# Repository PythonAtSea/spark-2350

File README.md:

# spark!2350

## What is this?

The spark!2350 is a RP2350 based microcontroller that has a RM2 chip for BLE and WiFi. It also has a LiPo battery charger, as it is designed for use in mireless keyboards. It also has a user accesable NeoPixel, and a variable charge rate. 

## Why?

I saw the release of the RM2 and I immediatly knew I wanted to make something with it. I've always thought the nice!nano was cool, so I kinda made that, although this is designed for maximum GPIO availibility, not small size. 

made with <3 and insanity.

## BOM

| Name | Link | Price |
|---|---|---|
| RPI RM2 | https://shop.pimoroni.com/products/raspberry-pi-radio-module | $4 |
| Pimoroni shpping | n/a | $14 |
| JLC PCBA | N/A | $78.28 |
| JLC shipping | N/A | $38.52 |
| Total | N/A | $134.80 |

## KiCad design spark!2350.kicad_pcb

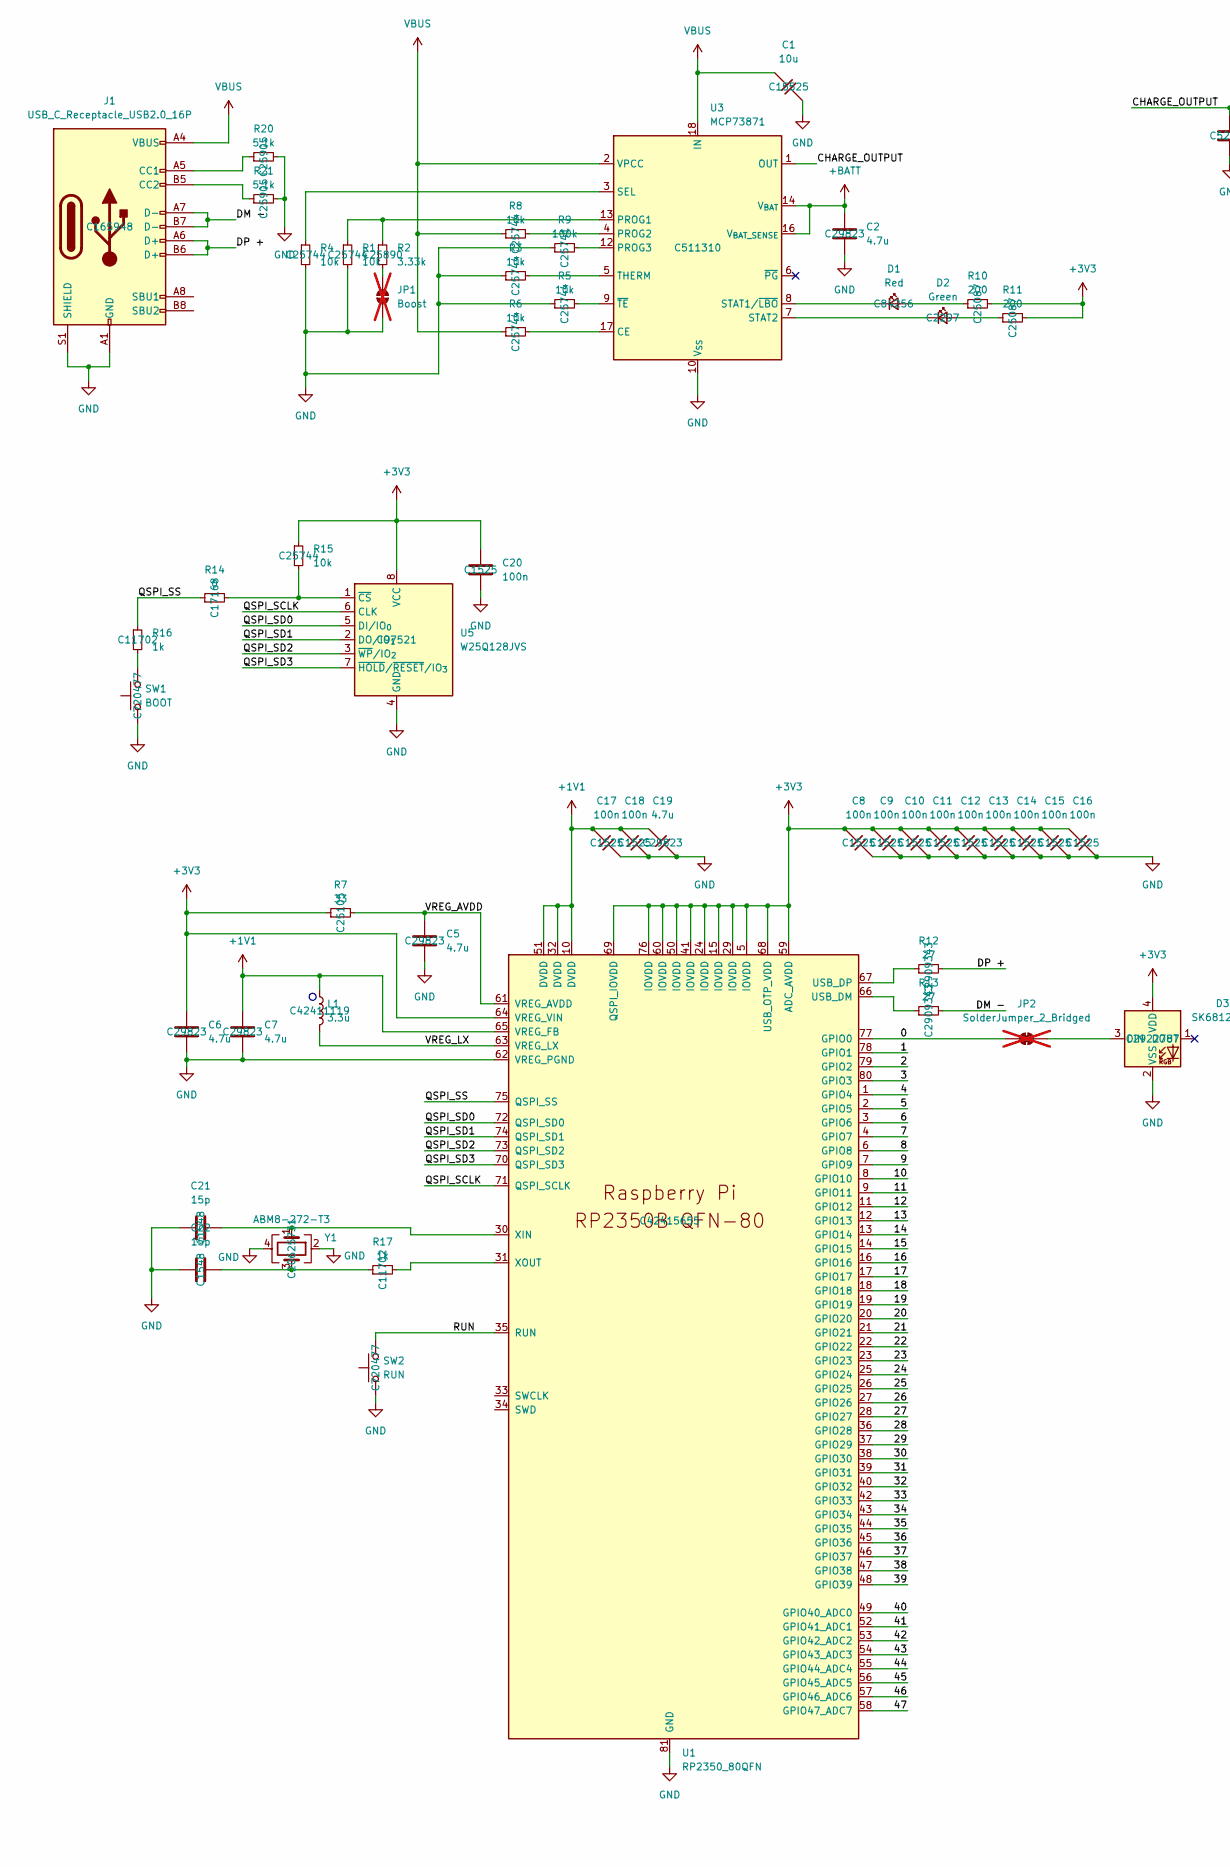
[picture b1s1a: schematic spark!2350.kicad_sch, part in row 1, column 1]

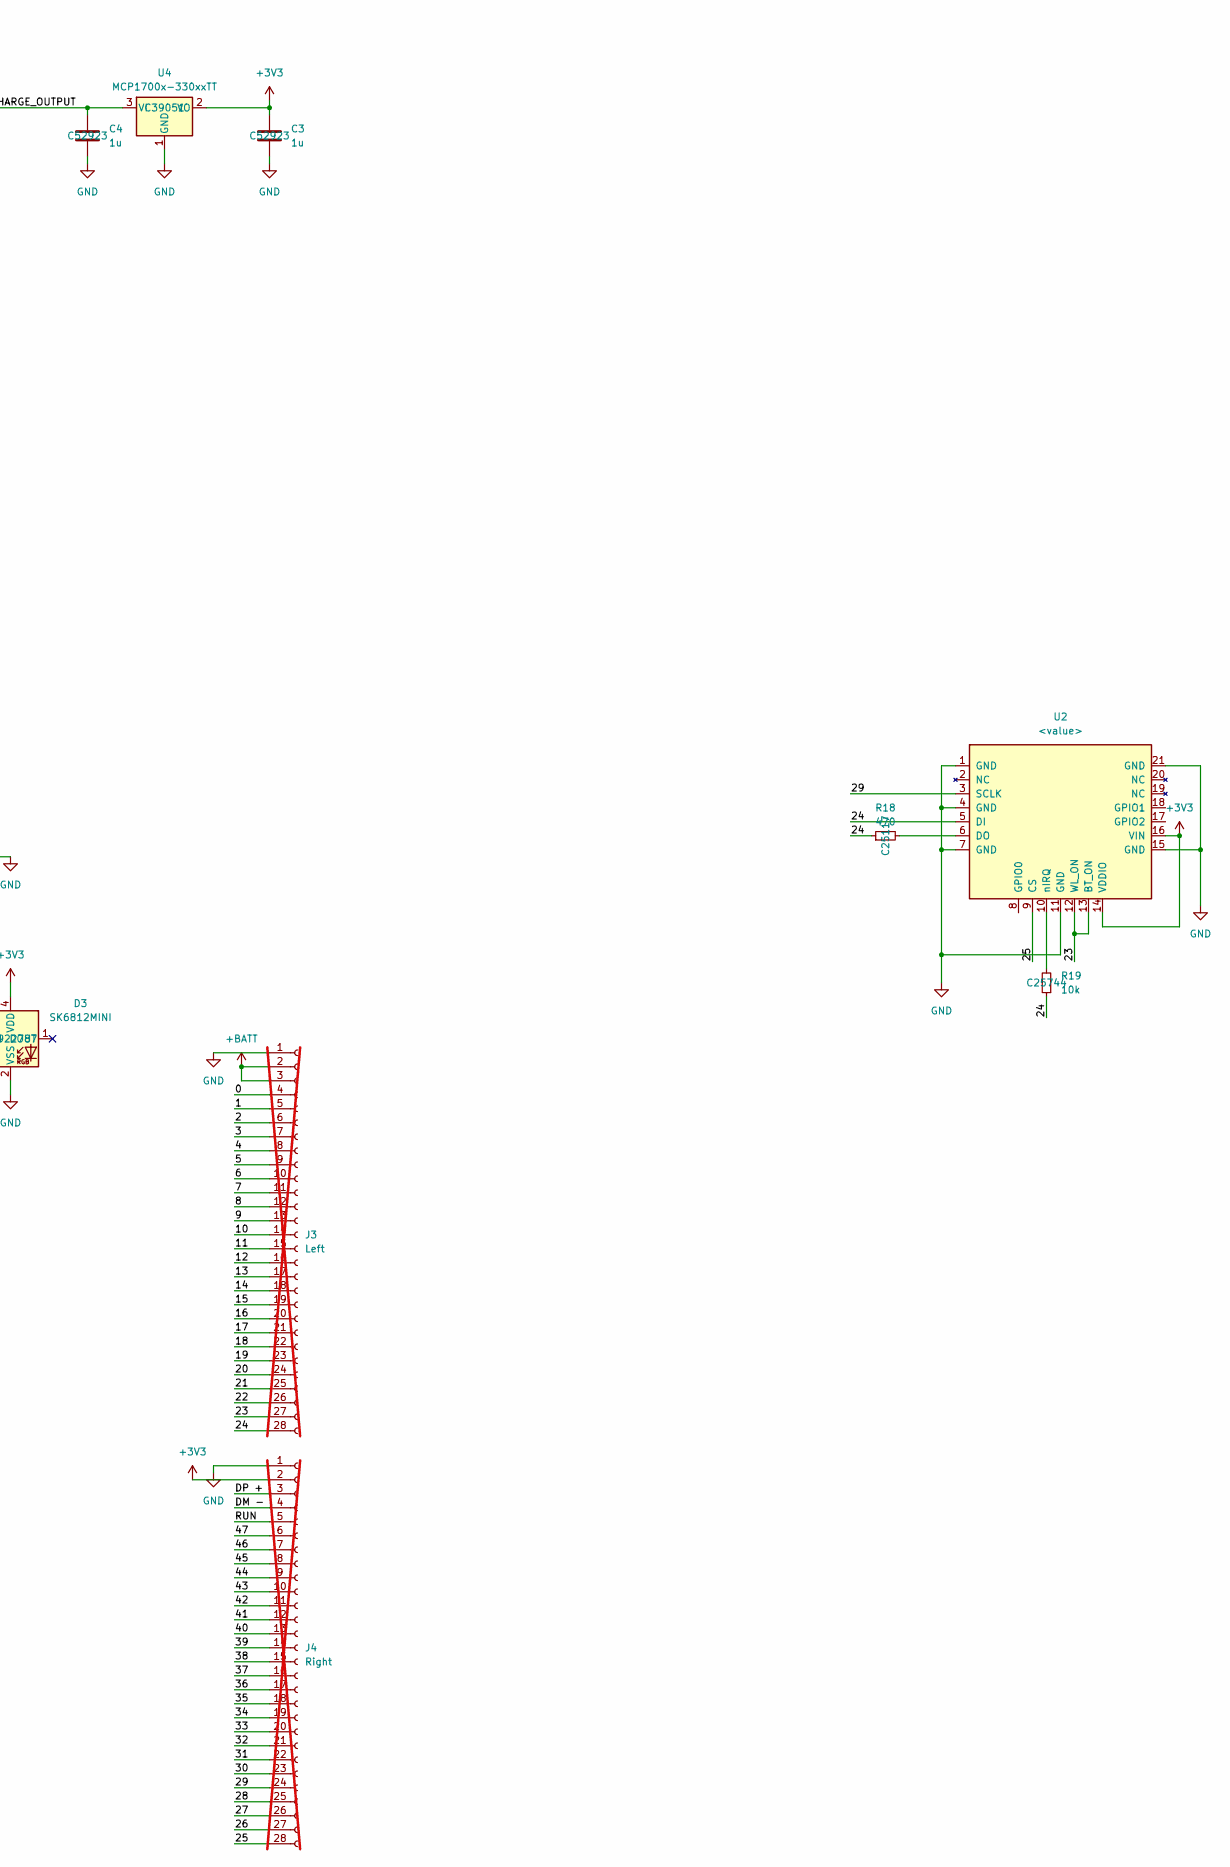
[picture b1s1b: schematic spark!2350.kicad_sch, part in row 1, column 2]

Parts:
C1: 10u; C_0402_1005Metric_small_pads; LCSC C15525
C2, C5, C6, C7, C19: 4.7u; C_0402_1005Metric_small_pads; LCSC C29823
C3, C4: 1u; C_0402_1005Metric_small_pads; LCSC C52923
C8, C9, C10, C11, C12, C13, C14, C15, C16, C17, C18, C20: 100n; C_0402_1005Metric_small_pads; LCSC C1525
C21, C22: 15p; C_0402_1005Metric_small_pads; LCSC C1548
D1: Red; LED_0805_2012Metric; LCSC C84256
D2: Green; LED_0805_2012Metric; LCSC C2297
D3: SK6812MINI; LED_SK6812MINI_PLCC4_3.5x3.5mm_P1.75mm; LCSC C2922787
J1: USB_C_Receptacle_USB2.0_16P; USB_C_Receptacle_HRO_TYPE-C-31-M-12; LCSC C165948
J3: Left; 27right; not fitted
J4: Right; 27left; not fitted
JP1: Boost; SolderJumper-2_P1.3mm_Open_RoundedPad1.0x1.5mm; not fitted
JP2: SolderJumper_2_Bridged; SolderJumper-2_P1.3mm_Bridged_RoundedPad1.0x1.5mm; not fitted
L1: 3.3u; L_pol_2016; LCSC C42411119
R1, R3, R4, R5, R6, R8, R15, R19: 10k; R_0402_1005Metric; LCSC C25744
R2: 3.33k; R_0402_1005Metric; LCSC C25890
R7: 33; R_0402_1005Metric; LCSC C25105
R9: 100k; R_0402_1005Metric; LCSC C25741
R10, R11: 200; R_0402_1005Metric; LCSC C25087
R12, R13: 27; R_0402_1005Metric; LCSC C2909343
R14: 0; R_0402_1005Metric; LCSC C17168
R16, R17: 1k; R_0402_1005Metric; LCSC C11702
R18: 470; R_0402_1005Metric; LCSC C25117
R20, R21: 5.1k; R_0402_1005Metric; LCSC C25905
SW1: BOOT; SW_TS-1088-AR02016; LCSC C720477
SW2: RUN; SW_TS-1088-AR02016; LCSC C720477
U1: RP2350_80QFN; RP2350-QFN-80-1EP_10x10_P0.4mm_EP3.4x3.4mm_ThermalVias; LCSC C42415655
U2: <value>; rpi_rmc20452t
U3: MCP73871; QFN-20-1EP_4x4mm_P0.5mm_EP2.5x2.5mm; LCSC C511310
U4: MCP1700x-330xxTT; SOT-23; LCSC C39051
U5: W25Q128JVS; SOIC-8_5.3x5.3mm_P1.27mm; LCSC C97521
Y1: ABM8-272-T3; ABM8-272-T3_ABR; LCSC C20625731

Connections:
+1V1: C7.1, C17.2, C18.2, C19.2, L1.1, U1.10 (DVDD), U1.32 (DVDD), U1.51 (DVDD), U1.65 (VREG_FB)
+3V3: C3.1, C6.1, C8.2, C9.2, C10.2, C11.2, C12.2, C13.2, C14.2, C15.2, C16.2, C20.1, D3.4 (VDD), J4.2, R7.1, R10.2, R11.2, R15.1, U1.5 (IOVDD), U1.15 (IOVDD), U1.24 (IOVDD), U1.29 (IOVDD), U1.41 (IOVDD), U1.50 (IOVDD), U1.59 (ADC_AVDD), U1.60 (IOVDD), U1.64 (VREG_VIN), U1.68 (USB_OTP_VDD), U1.69 (QSPI_IOVDD), U1.76 (IOVDD), U2.14 (VDDIO), U2.16 (VIN), U4.2 (VO), U5.8 (VCC)
+BATT: C2.1, J3.2, J3.3, U3.14 (V_{BAT}), U3.15 (V_{BAT}), U3.16 (V_{BAT_SENSE})
/0: J3.4, JP2.1 (A), U1.77 (GPIO0)
/1: J3.5, U1.78 (GPIO1)
/2: J3.6, U1.79 (GPIO2)
/3: J3.7, U1.80 (GPIO3)
/4: J3.8, U1.1 (GPIO4)
/5: J3.9, U1.2 (GPIO5)
/6: J3.10, U1.3 (GPIO6)
/7: J3.11, U1.4 (GPIO7)
/8: J3.12, U1.6 (GPIO8)
/9: J3.13, U1.7 (GPIO9)
/10: J3.14, U1.8 (GPIO10)
/11: J3.15, U1.9 (GPIO11)
/12: J3.16, U1.11 (GPIO12)
/13: J3.17, U1.12 (GPIO13)
/14: J3.18, U1.13 (GPIO14)
/15: J3.19, U1.14 (GPIO15)
/16: J3.20, U1.16 (GPIO16)
/17: J3.21, U1.17 (GPIO17)
/18: J3.22, U1.18 (GPIO18)
/19: J3.23, U1.19 (GPIO19)
/20: J3.24, U1.20 (GPIO20)
/21: J3.25, U1.21 (GPIO21)
/22: J3.26, U1.22 (GPIO22)
/23: J3.27, U1.23 (GPIO23), U2.12 (WL_ON), U2.13 (BT_ON)
/24: J3.28, R18.1, R19.1, U1.25 (GPIO24), U2.5 (DI)
/25: J4.28, U1.26 (GPIO25), U2.9 (CS)
/26: J4.27, U1.27 (GPIO26)
/27: J4.26, U1.28 (GPIO27)
/28: J4.25, U1.36 (GPIO28)
/29: J4.24, U1.37 (GPIO29), U2.3 (SCLK)
/30: J4.23, U1.38 (GPIO30)
/31: J4.22, U1.39 (GPIO31)
/32: J4.21, U1.40 (GPIO32)
/33: J4.20, U1.42 (GPIO33)
/34: J4.19, U1.43 (GPIO34)
/35: J4.18, U1.44 (GPIO35)
/36: J4.17, U1.45 (GPIO36)
/37: J4.16, U1.46 (GPIO37)
/38: J4.15, U1.47 (GPIO38)
/39: J4.14, U1.48 (GPIO39)
/40: J4.13, U1.49 (GPIO40_ADC0)
/41: J4.12, U1.52 (GPIO41_ADC1)
/42: J4.11, U1.53 (GPIO42_ADC2)
/43: J4.10, U1.54 (GPIO43_ADC3)
/44: J4.9, U1.55 (GPIO44_ADC4)
/45: J4.8, U1.56 (GPIO45_ADC5)
/46: J4.7, U1.57 (GPIO46_ADC6)
/47: J4.6, U1.58 (GPIO47_ADC7)
/CHARGE_OUTPUT: C4.1, U3.1 (OUT), U3.20 (OUT), U4.3 (VI)
/DM -: J1.A7 (D-), J1.B7 (D-), J4.4, R13.2
/DP +: J1.A6 (D+), J1.B6 (D+), J4.3, R12.2
/QSPI_SCLK: U1.71 (QSPI_SCLK), U5.6 (CLK)
/QSPI_SD0: U1.72 (QSPI_SD0), U5.5 (DI/IO_{0})
/QSPI_SD1: U1.74 (QSPI_SD1), U5.2 (DO/IO_{1})
/QSPI_SD2: U1.73 (QSPI_SD2), U5.3 (~WP/IO_{2})
/QSPI_SD3: U1.70 (QSPI_SD3), U5.7 (~HOLD/~RESET/IO_{3})
/QSPI_SS: R14.1, R16.1, U1.75 (QSPI_SS)
/RUN: J4.5, SW2.2, U1.35 (RUN)
/VREG_AVDD: C5.1, R7.2, U1.61 (VREG_AVDD)
/VREG_LX: L1.2, U1.63 (VREG_LX)
GND: C1.1, C2.2, C3.2, C4.2, C5.2, C6.2, C7.2, C8.1, C9.1, C10.1, C11.1, C12.1, C13.1, C14.1, C15.1, C16.1, C17.1, C18.1, C19.1, C20.2, C21.1, C22.1, D3.2 (VSS), J1.A1 (GND), J1.A12 (GND), J1.B1 (GND), J1.B12 (GND), J1.S1 (SHIELD), J3.1, J4.1, JP1.1 (A), R1.2, R3.1, R4.2, R5.1, R9.1, R20.2, R21.2, SW1.1, SW2.1, U1.62 (VREG_PGND), U1.81 (GND), U2.1 (GND), U2.4 (GND), U2.7 (GND), U2.11 (GND), U2.15 (GND), U2.21 (GND), U3.10 (V_{SS}), U3.11 (V_{SS}), U3.21 (V_{SS}), U4.1 (GND), U5.4 (GND), Y1.2, Y1.4
unnamed: C22.2, R17.1, Y1.3
unnamed: D1.2 (A), R10.1
unnamed: D1.1 (K), U3.8 (STAT1/~LBO)
unnamed: D2.2 (A), R11.1
unnamed: D2.1 (K), U3.7 (STAT2)
unnamed: D3.3 (DIN), JP2.2 (B)
unnamed: J1.A5 (CC1), R20.1
unnamed: J1.B5 (CC2), R21.1
unnamed: JP1.2 (B), R2.2
unnamed: R16.2, SW1.2
unnamed: R13.1, U1.66 (USB_DM)
unnamed: R12.1, U1.67 (USB_DP)
unnamed: C21.2, U1.30 (XIN), Y1.1
unnamed: R17.2, U1.31 (XOUT)
unnamed: R18.2, U2.6 (DO)
unnamed: R19.2, U2.10 (nIRQ)
unnamed: R6.2, U3.17 (CE)
unnamed: R1.1, R2.1, U3.13 (PROG1)
unnamed: R8.2, U3.4 (PROG2)
unnamed: R9.2, U3.12 (PROG3)
unnamed: R4.1, U3.3 (SEL)
unnamed: R3.2, U3.5 (THERM)
unnamed: R5.2, U3.9 (~TE)
unnamed: R14.2, R15.2, U5.1 (~CS)
VBUS: C1.2, J1.A4 (VBUS), J1.A9 (VBUS), J1.B4 (VBUS), J1.B9 (VBUS), R6.1, R8.1, U3.2 (VPCC), U3.18 (IN), U3.19 (IN)

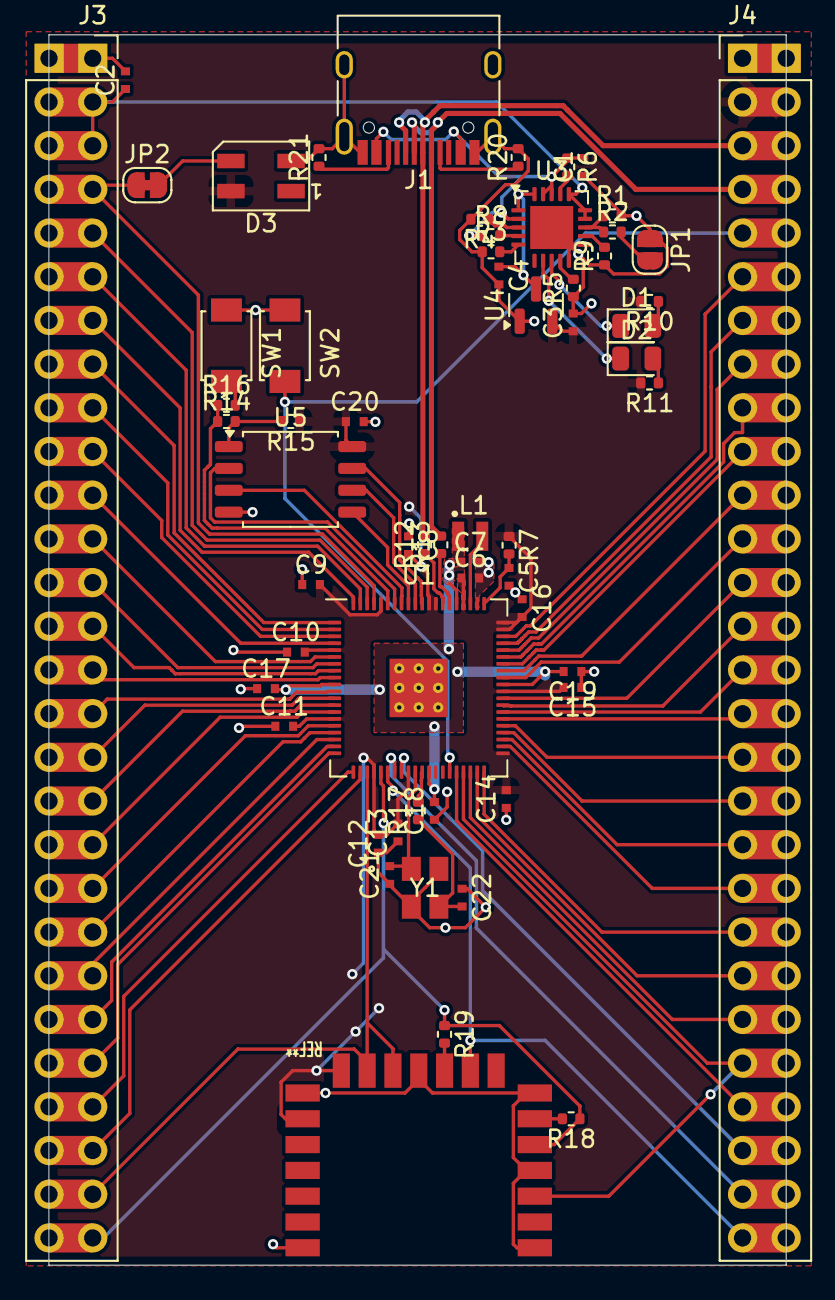
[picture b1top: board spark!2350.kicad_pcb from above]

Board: 2 copper layers, 42.9 x 71.5 mm, 60 parts (0 on the bottom side), 89 nets.

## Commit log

2025-07-19 first commit!
2025-07-19 words.
2025-07-19 pictures!
2025-07-22 thingamagig
2025-07-29 fix(?) images
2025-07-30 pcb started yay!
2025-08-01 i kinda forgot to bump hardware files regularly so here ya go!
2025-08-01 hour count
2025-08-01 yeehaw
2025-08-01 little steps (files)
2025-08-01 schematic :facepalm:
2025-08-08 linkity link link
